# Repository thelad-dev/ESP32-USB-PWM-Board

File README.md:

# ESP32 PWM- / Tacho-Board (4-Pin-Luefter)

## Varianten

| Variante | Beschreibung | Hardware | Firmware |
|----------|--------------|----------|----------|
| v1 (1 Kanal) | ESP32-DevKitC, ein Luefterkanal | [writeup.md](writeup.md) Teil A, [hardware/bom-1channel.csv](hardware/bom-1channel.csv) | [legacy/1ch/](legacy/1ch/) |
| **v2 (4 Kanal + Temp)** | ESP32-C6 SuperMini gesteckt, 4x PWM/Tach, DS18B20 | [hardware/v2-c6-4ch/](hardware/v2-c6-4ch/) | `src/`, `include/` |

Entscheidung: **C6** wegen Bestand (9x). C3-SuperMini ist pin-inkompatibel (2x8 vs 2x10) - siehe [INVENTORY-DECISIONS.md](hardware/v2-c6-4ch/INVENTORY-DECISIONS.md).

## Firmware v2 (PlatformIO)

```bash
pio run -e esp32-c6-supermini -t upload
pio device monitor -e esp32-c6-supermini
```

Baud **115200**. Pins in `include/config.h` (PWM 0/1/2/3, Tach 20/19/18/14, Temp 21).

### Serielle Befehle

| Befehl | Wirkung |
|--------|---------|
| `PWM 0` / `PWM <5-100>` | Handbetrieb fuer alle Kanaele, 5 Minuten |
| `PWM ALL <0-100>` | Handbetrieb fuer alle Kanaele, auch bei 1-4%, 5 Minuten |
| `PWM <1-4> <0-100>` | ein Kanal im Handbetrieb fuer 5 Minuten |
| `RPM` / `RPM <1-4>` | Drehzahl |
| `TEMP` | DS18B20 °C |
| `STATUS` | PWM, RPM, Temp |
| `HELP` | Hilfe |

Unvollstaendige oder fehlerhafte `PWM`-Argumente werden abgelehnt, ohne die
Luefterwerte zu aendern. Ein einzelnes `PWM 1` ist daher kein All-Kanaele-Befehl.

Im Automatikbetrieb gilt eine stufige Temperaturkurve: unter 40 °C 35 %, ab
40/45/50/55 °C 50/65/80/100 %. Beim Abkuehlen wird jede Stufe erst 2 °C unter
ihrer Einschaltschwelle verlassen. 35 % ist die Mindestvorgabe. Ein fehlender
oder ungueltiger Sensorwert setzt alle Kanaele sofort auf 100 % und uebersteuert
auch den Handbetrieb. `STATUS` zeigt `AUTO`, `MANUAL` oder `FAILSAFE` pro Kanal.

## Bestellbares PCB (v2)

- Gerber: `hardware/v2-c6-4ch/fab/JLCPCB-gerbers-esp32-c6-pwm-4ch.zip`
- BOM + Stock-Spalte: `hardware/v2-c6-4ch/bom.csv`
- Handloeten: `hardware/v2-c6-4ch/HAND_SOLDER.md`
- Bestell-Absatz: `hardware/v2-c6-4ch/ORDER.md`

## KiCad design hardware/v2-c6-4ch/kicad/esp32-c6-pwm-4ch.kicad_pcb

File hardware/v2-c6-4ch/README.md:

# v2: 4-Kanal PWM/Tacho + DS18B20 (ESP32-C6 SuperMini)

- `bom.csv` - Stueckliste mit LCSC und Spalte Stock (vorhanden/zu bestellen)
- `INVENTORY-DECISIONS.md` - C6 vs C3, MOSFET-Modul, Levelshifter
- `fab/JLCPCB-gerbers-esp32-c6-pwm-4ch.zip` - Fertigungsdaten
- `fab/cpl-smd.csv` - optionale SMD-Platzierung
- `ORDER.md` / `HAND_SOLDER.md`
- `kicad/esp32-c6-pwm-4ch.kicad_pcb`
- `scripts/build_pcb.py`

Schaltung und 1-Wire-Anschlussregel: `../../writeup.md` Teil B; Bestückung und
Anschluss der Sensorvarianten: `HAND_SOLDER.md`.

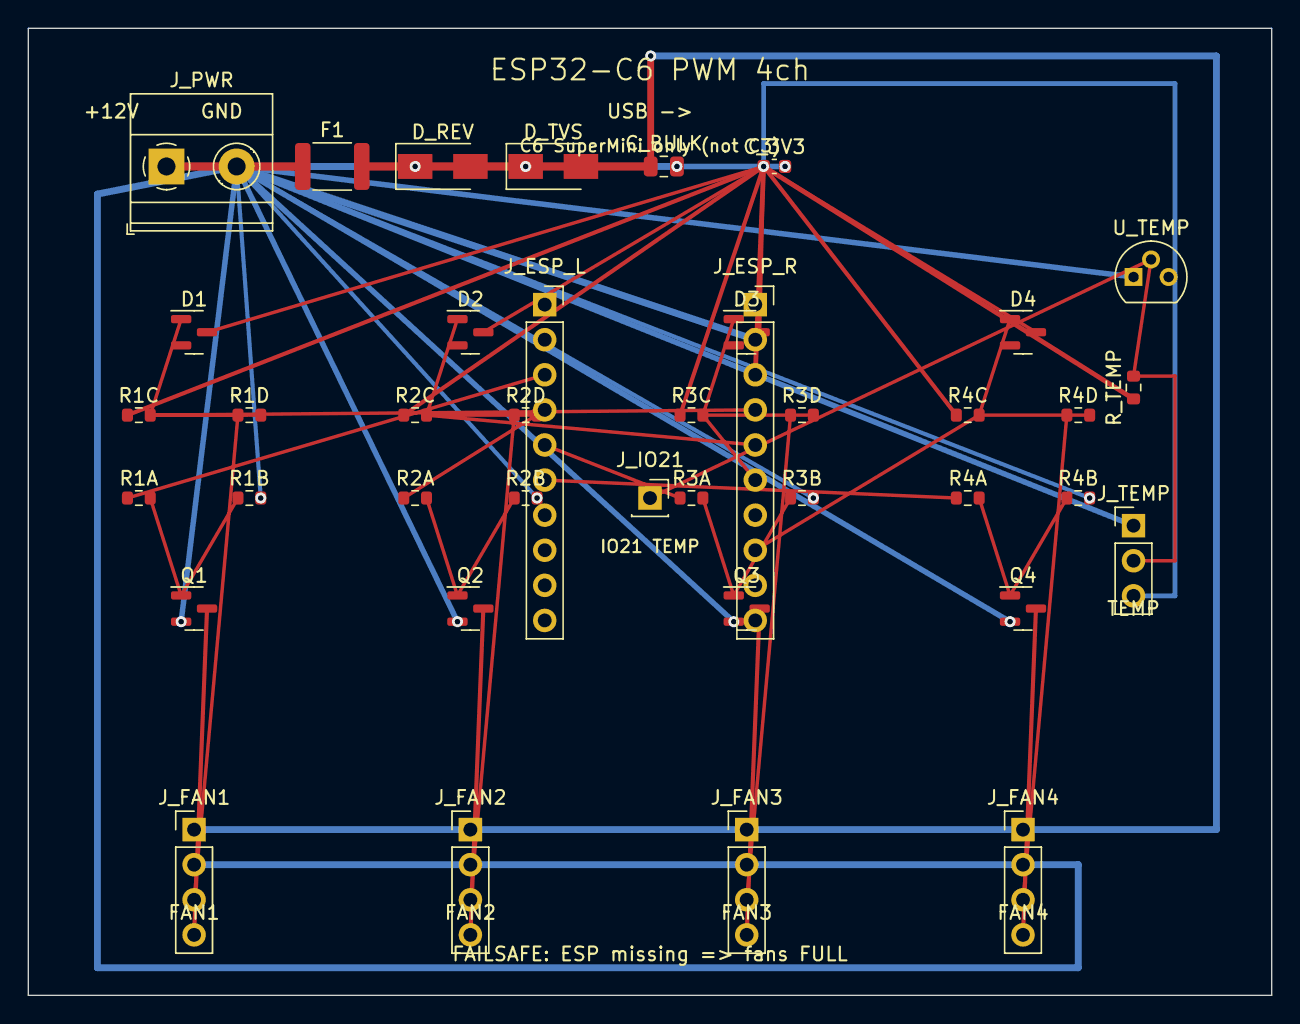
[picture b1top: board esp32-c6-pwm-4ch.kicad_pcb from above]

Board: 2 copper layers, 90.0 x 70.0 mm, 40 parts (0 on the bottom side), 25 nets.

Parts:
C_3V3: 100n; C_0603_1608Metric
C_BULK: 10u; C_0805_2012Metric
D1, D2, D3, D4: BAT54S; SOT-23
D_REV: SS34; D_SMA
D_TVS: SMAJ15A; D_SMA
F1: PTC_3A_30V; Fuse_1812_4532Metric
J_ESP_L: Socket_1x10; PinSocket_1x10_P2.54mm_Vertical
J_ESP_R: Socket_1x10; PinSocket_1x10_P2.54mm_Vertical
J_FAN1, J_FAN2, J_FAN3, J_FAN4: 2510-4A; PinHeader_1x04_P2.54mm_Vertical
J_IO21: Socket_1x01; PinSocket_1x01_P2.54mm_Vertical
J_PWR: KF128_5.08_2P; TerminalBlock_Phoenix_MKDS-1,5-2-5.08_1x02_P5.08mm_Horizont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
J_TEMP: PROBE_1x3; PinHeader_1x03_P2.54mm_Vertical
Q1, Q2, Q3, Q4: AO3400A; SOT-23
R1A, R2A, R3A, R4A: 100; R_0603_1608Metric
R1B, R2B, R3B, R4B: 100k; R_0603_1608Metric
R1C, R2C, R3C, R4C: 10k; R_0603_1608Metric
R1D, R2D, R3D, R4D: 1k; R_0603_1608Metric
R_TEMP: 4.7k; R_0603_1608Metric
U_TEMP: DS18B20+; TO-92

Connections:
+3V3: C_3V3.1, D1.2, D1.3, D2.2, D2.3, D3.2, D3.3, D4.2, D4.3, J_ESP_R.3, J_TEMP.3, R1C.1, R2C.1, R3C.1, R4C.1, R_TEMP.1, U_TEMP.3
+12V: F1.1, J_PWR.1
+12V_F: C_BULK.1, D_REV.2, D_TVS.2, F1.2, J_FAN1.1, J_FAN2.1, J_FAN3.1, J_FAN4.1
FAN1_PWM: J_FAN1.4, Q1.3
FAN2_PWM: J_FAN2.4, Q2.3
FAN3_PWM: J_FAN3.4, Q3.3
FAN4_PWM: J_FAN4.4, Q4.3
GATE1: Q1.1, R1A.2, R1B.1
GATE2: Q2.1, R2A.2, R2B.1
GATE3: Q3.1, R3A.2, R3B.1
GATE4: Q4.1, R4A.2, R4B.1
GND: C_3V3.2, C_BULK.2, D_REV.1, D_TVS.1, J_ESP_R.2, J_FAN1.2, J_FAN2.2, J_FAN3.2, J_FAN4.2, J_PWR.2, J_TEMP.1, Q1.2, Q2.2, Q3.2, Q4.2, R1B.2, R2B.2, R3B.2, R4B.2, U_TEMP.1
PWM1: J_ESP_L.3, R1A.1
PWM2: J_ESP_L.4, R2A.1
PWM3: J_ESP_L.5, R3A.1
PWM4: J_ESP_L.6, R4A.1
TACH1: J_FAN1.3, R1D.1
TACH1_GPIO: D1.1, J_ESP_R.4, R1C.2, R1D.2
TACH2: J_FAN2.3, R2D.1
TACH2_GPIO: D2.1, J_ESP_R.5, R2C.2, R2D.2
TACH3: J_FAN3.3, R3D.1
TACH3_GPIO: D3.1, J_ESP_R.6, R3C.2, R3D.2
TACH4: J_FAN4.3, R4D.1
TACH4_GPIO: D4.1, J_ESP_R.8, R4C.2, R4D.2
TEMP_DQ: J_IO21.1, J_TEMP.2, R_TEMP.2, U_TEMP.2
